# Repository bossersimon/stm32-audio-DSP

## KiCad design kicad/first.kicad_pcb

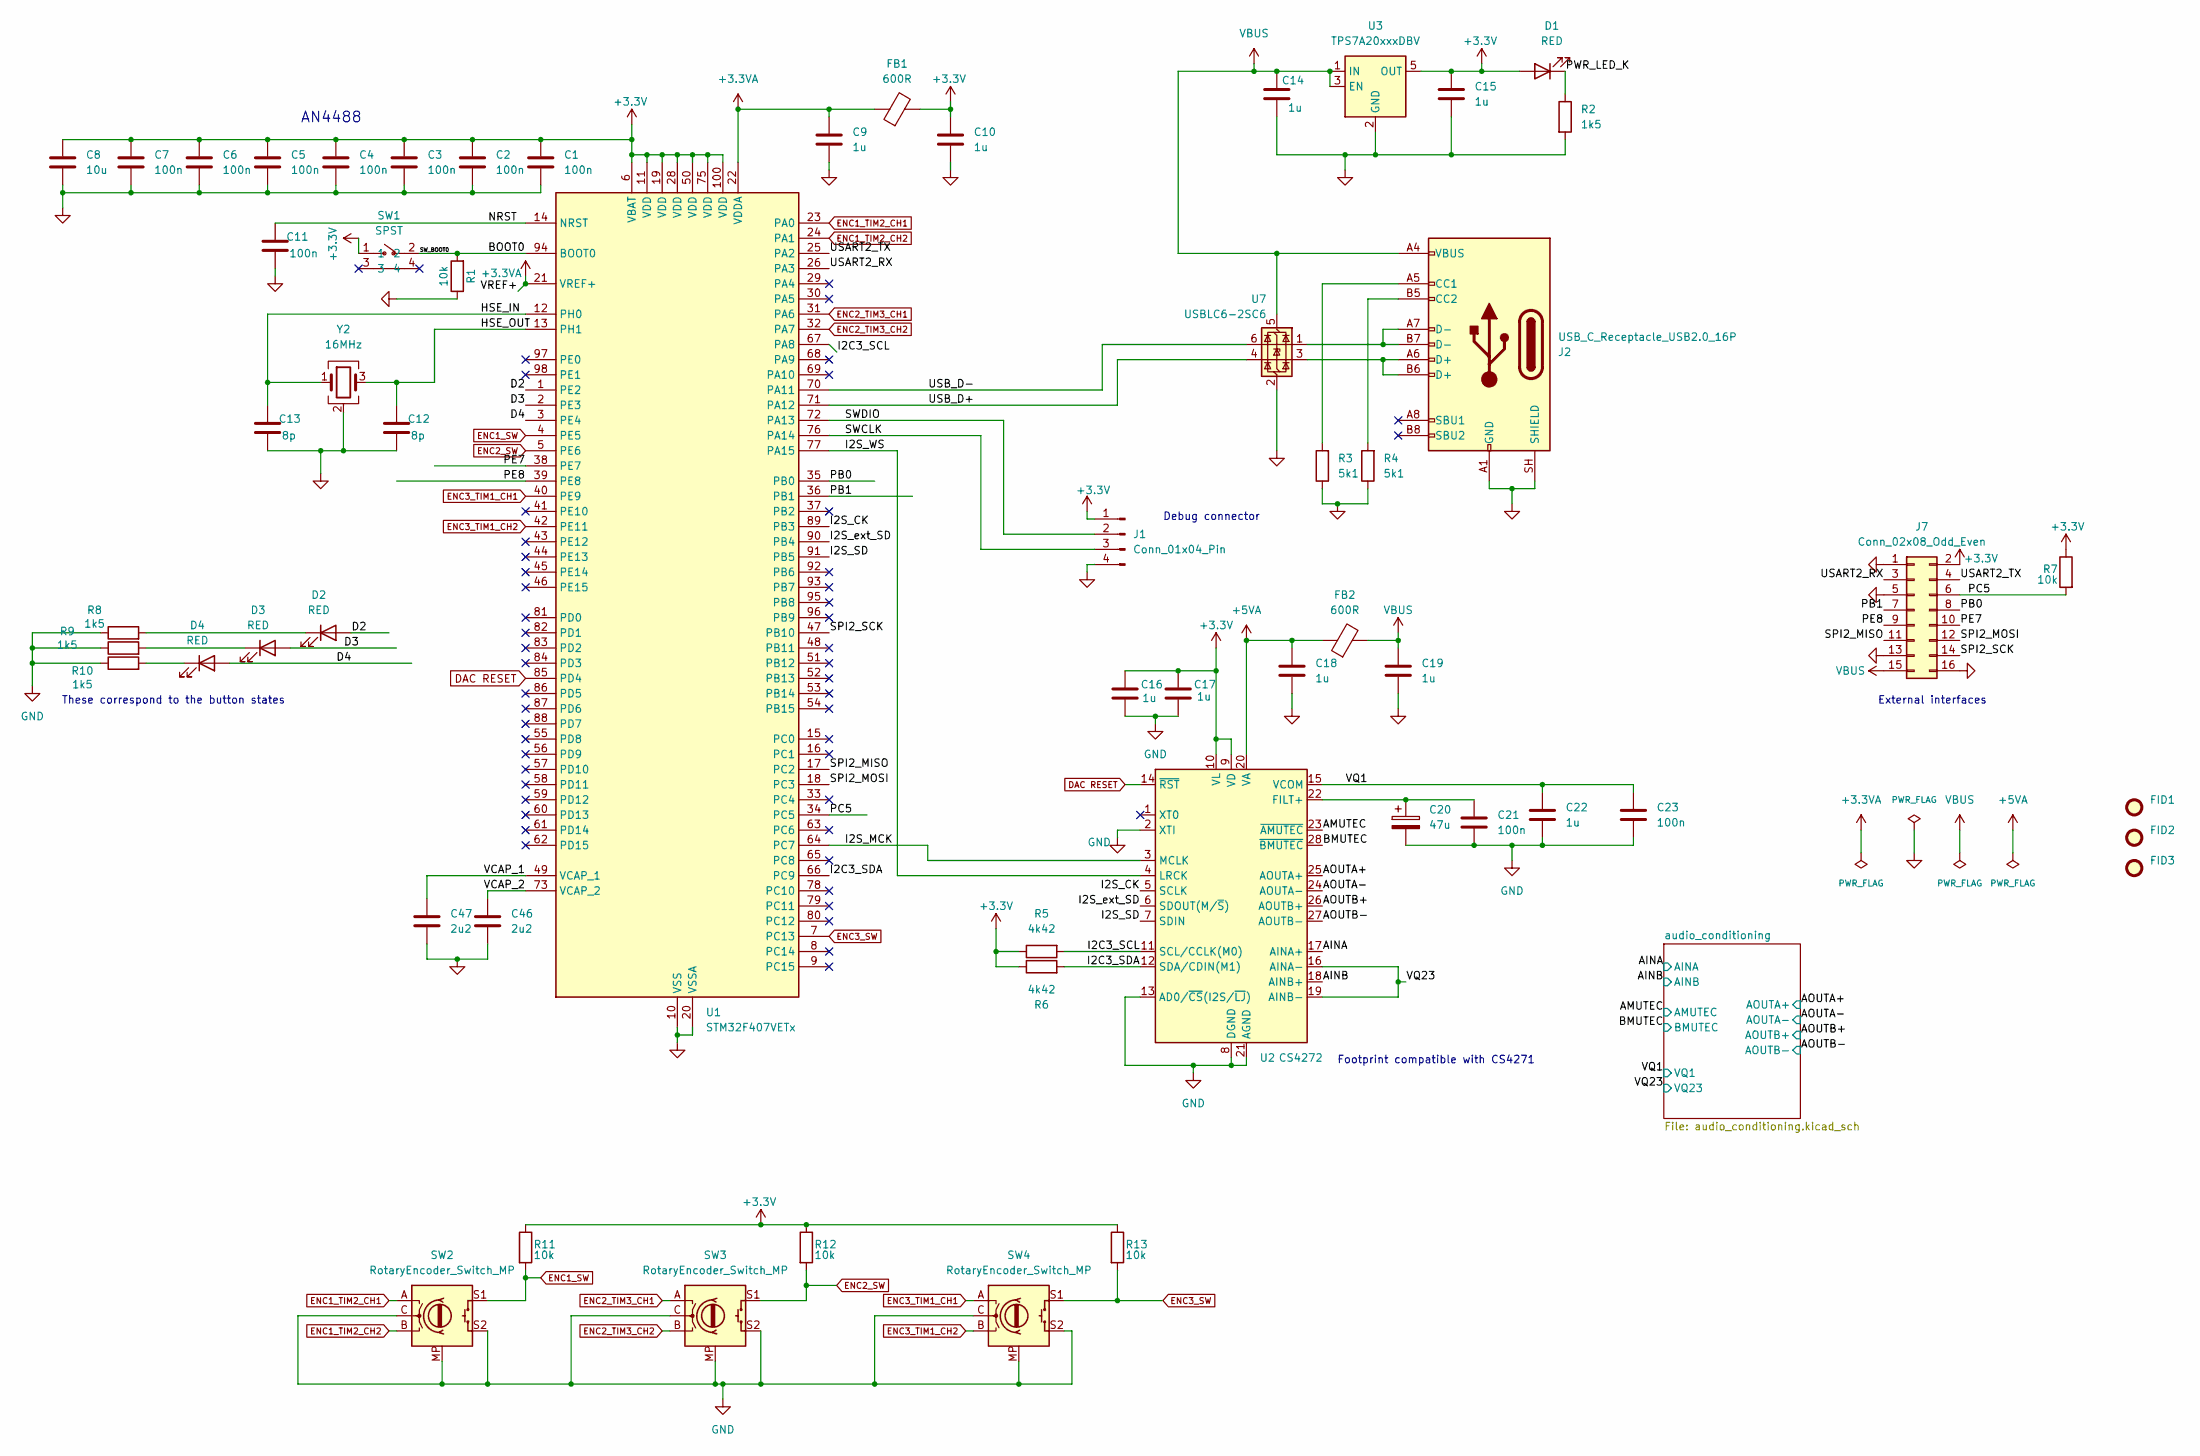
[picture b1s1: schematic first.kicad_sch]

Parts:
C1, C2, C3, C4, C5, C6, C7, C11, C21, C23: 100n; C_0402_1005Metric
C8: 10u; C_0603_1608Metric
C9, C10, C14, C15, C16, C17, C18, C19, C22: 1u; C_0402_1005Metric
C12, C13: 8p; C_0402_1005Metric
C20: 47u; CP_Elec_4x5.4
C46, C47: 2u2; C_0402_1005Metric
D1, D2, D3, D4: RED; LED_0603_1608Metric
FB1, FB2: 600R; L_0603_1608Metric
FID1, FID2, FID3: Fiducial; Fiducial_1mm_Mask3mm
J1: Conn_01x04_Pin; PinHeader_1x04_P2.54mm_Vertical
J2: USB_C_Receptacle_USB2.0_16P; USB_C_Receptacle_G-Switch_GT-USB-7010ASV
J7: Conn_02x08_Odd_Even; PinHeader_2x08_P2.54mm_Vertical
R1, R7, R11, R12, R13: 10k; R_0402_1005Metric
R2, R8, R9, R10: 1k5; R_0402_1005Metric
R3, R4: 5k1; R_0402_1005Metric
R5, R6: 4k42; R_0402_1005Metric
SW1: SPST; SW-SMD_TC-S3601-3.5-260G-F0.6; MPN TC-S3601-3.5-260G-F0.6; LCSC Part C49101620
SW2, SW3, SW4: RotaryEncoder_Switch_MP; RotaryEncoder_Alps_EC11E-Switch_Vertical_H20mm
U1: STM32F407VETx; LQFP-100_14x14mm_P0.5mm
U2: CS4272; TSSOP-28_4.4x9.7mm_P0.65mm
U3: TPS7A20xxxDBV; SOT-23-5
U7: USBLC6-2SC6; SOT-23-6
Y2: 16MHz; Crystal_SMD_3225-4Pin_3.2x2.5mm

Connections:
+3.3V: C1.1, C2.1, C3.1, C4.1, C5.1, C6.1, C7.1, C8.1, C10.1, C15.1, C16.1, C17.1, D1.2 (A), FB1.2, J1.1, J7.2, R5.1, R6.1, R7.1, R11.1, R12.1, R13.1, SW1.1, U1.6 (VBAT), U1.11 (VDD), U1.19 (VDD), U1.28 (VDD), U1.50 (VDD), U1.75 (VDD), U1.100 (VDD), U2.9 (VD), U2.10 (VL), U3.5 (OUT)
+3.3VA: C9.1, FB1.1, U1.21 (VREF+), U1.22 (VDDA)
+5VA: C18.1, FB2.1, U2.20 (VA); also elsewhere on the board
/AINA: U2.17 (AINA+); also elsewhere on the board
/AINB: U2.18 (AINB+); also elsewhere on the board
/AMUTEC: U2.23 (~AMUTEC); also elsewhere on the board
/AOUTA+: U2.25 (AOUTA+); also elsewhere on the board
/AOUTA-: U2.24 (AOUTA-); also elsewhere on the board
/AOUTB+: U2.26 (AOUTB+); also elsewhere on the board
/AOUTB-: U2.27 (AOUTB-); also elsewhere on the board
/BMUTEC: U2.28 (~BMUTEC); also elsewhere on the board
/BOOT0: R1.2, SW1.2, U1.94 (BOOT0)
/D2: D2.2 (A), U1.1 (PE2)
/D3: D3.2 (A), U1.2 (PE3)
/D4: D4.2 (A), U1.3 (PE4)
/HSE_IN: C13.1, U1.12 (PH0), Y2.1
/HSE_OUT: C12.1, U1.13 (PH1), Y2.3
/I2C3_SCL: R5.2, U1.67 (PA8), U2.11 (SCL/CCLK(M0))
/I2C3_SDA: R6.2, U1.66 (PC9), U2.12 (SDA/CDIN(M1))
/I2S_CK: U1.89 (PB3), U2.5 (SCLK)
/I2S_MCK: U1.64 (PC7), U2.3 (MCLK)
/I2S_SD: U1.91 (PB5), U2.7 (SDIN)
/I2S_WS: U1.77 (PA15), U2.4 (LRCK)
/I2S_ext_SD: U1.90 (PB4), U2.6 (SDOUT(M/~S))
/NRST: C11.1, U1.14 (NRST)
/PB0: J7.8, U1.35 (PB0)
/PB1: J7.7, U1.36 (PB1)
/PC5: J7.6, R7.2, U1.34 (PC5)
/PE7: J7.10, U1.38 (PE7)
/PE8: J7.9, U1.39 (PE8)
/PWR_LED_K: D1.1 (K), R2.1
/SPI2_MISO: J7.11, U1.17 (PC2)
/SPI2_MOSI: J7.12, U1.18 (PC3)
/SPI2_SCK: J7.14, U1.47 (PB10)
/SWCLK: J1.3, U1.76 (PA14)
/SWDIO: J1.2, U1.72 (PA13)
/USART2_RX: J7.3, U1.26 (PA3)
/USART2_TX: J7.4, U1.25 (PA2)
/USB_D+: U1.71 (PA12), U7.4 (I/O2)
/USB_D-: U1.70 (PA11), U7.6 (I/O1)
/VCAP_1: C47.2, U1.49 (VCAP_1)
/VCAP_2: C46.2, U1.73 (VCAP_2)
/VQ1: C22.1, C23.1, U2.15 (VCOM); also elsewhere on the board
/VQ23: U2.16 (AINA-), U2.19 (AINB-); also elsewhere on the board
DAC RESET: U1.85 (PD4), U2.14 (~RST)
ENC1_SW: R11.2, SW2.S1, U1.4 (PE5)
ENC1_TIM2_CH1: SW2.A, U1.23 (PA0)
ENC1_TIM2_CH2: SW2.B, U1.24 (PA1)
ENC2_SW: R12.2, SW3.S1, U1.5 (PE6)
ENC2_TIM3_CH1: SW3.A, U1.31 (PA6)
ENC2_TIM3_CH2: SW3.B, U1.32 (PA7)
ENC3_SW: R13.2, SW4.S1, U1.7 (PC13)
ENC3_TIM1_CH1: SW4.A, U1.40 (PE9)
ENC3_TIM1_CH2: SW4.B, U1.42 (PE11)
GND: C1.2, C2.2, C3.2, C4.2, C5.2, C6.2, C7.2, C8.2, C9.2, C10.2, C11.2, C12.2, C13.2, C14.2, C15.2, C16.2, C17.2, C18.2, C19.2, C20.2, C21.2, C22.2, C23.2, C46.1, C47.1, J1.4, J2.A1 (GND), J2.A12 (GND), J2.B1 (GND), J2.B12 (GND), J2.SH (SHIELD), J7.1, J7.5, J7.13, J7.16, R1.1, R2.2, R3.1, R4.1, R8.1, R9.1, R10.1, SW2.C, SW2.MP, SW2.S2, SW3.C, SW3.MP, SW3.S2, SW4.C, SW4.MP, SW4.S2, U1.10 (VSS), U1.20 (VSSA), U1.27 (VSS), U1.74 (VSS), U1.99 (VSS), U2.2 (XTI), U2.8 (DGND), U2.13 (AD0/~CS(I2S/~LJ)), U2.21 (AGND), U3.2 (GND), U7.2 (GND), Y2.2 (G), Y2.4 (G); also elsewhere on the board
unnamed: D2.1 (K), R8.2
unnamed: D3.1 (K), R9.2
unnamed: D4.1 (K), R10.2
unnamed: J2.A5 (CC1), R3.2
unnamed: J2.B5 (CC2), R4.2
unnamed: J2.A6 (D+), J2.B6 (D+), U7.3 (I/O2)
unnamed: J2.A7 (D-), J2.B7 (D-), U7.1 (I/O1)
unnamed: C20.1, C21.1, U2.22 (FILT+)
VBUS: C14.1, C19.1, FB2.2, J2.A4 (VBUS), J2.A9 (VBUS), J2.B4 (VBUS), J2.B9 (VBUS), J7.15, U3.1 (IN), U3.3 (EN), U7.5 (VBUS)

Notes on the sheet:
AN4488
These correspond to the button states
Footprint compatible with CS4271
Debug connector
External interfaces

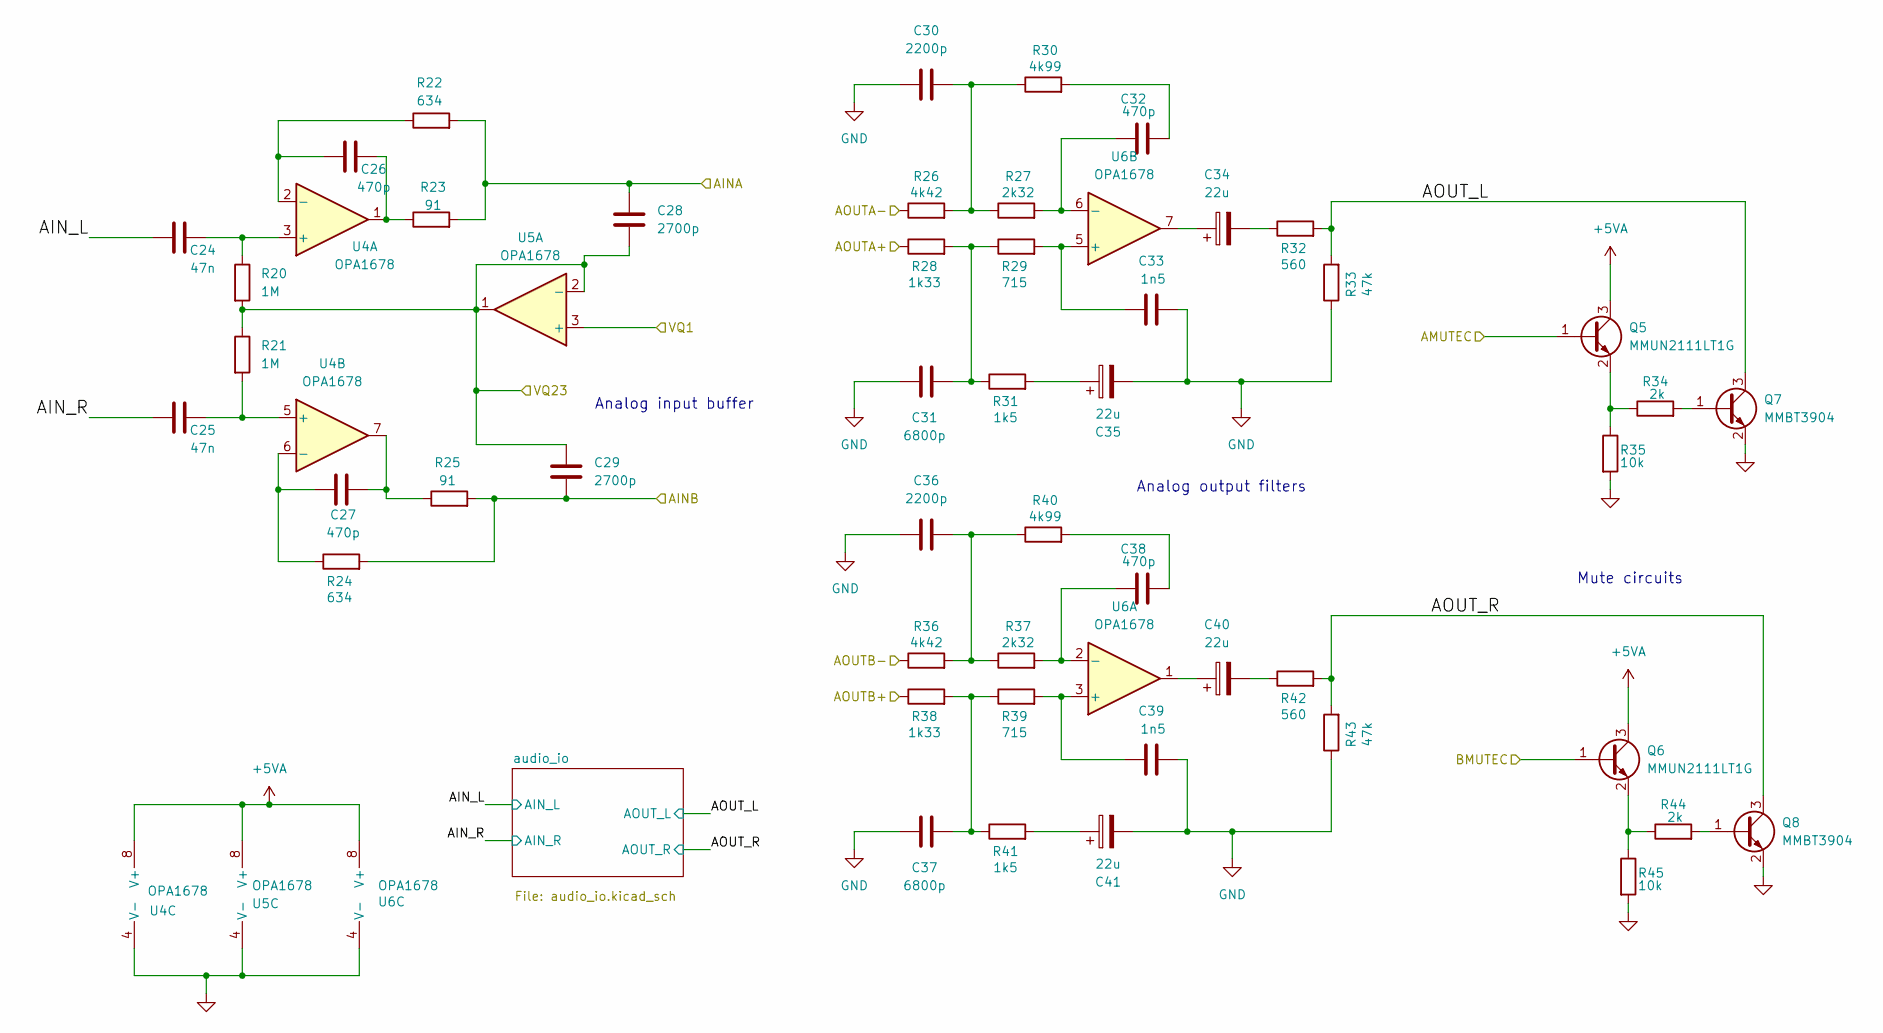
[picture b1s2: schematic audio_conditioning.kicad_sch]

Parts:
C24, C25: 47n; C_0805_2012Metric
C26, C27, C32, C38: 470p; C_0402_1005Metric
C28, C29: 2700p; C_0603_1608Metric
C30, C36: 2200p; C_0603_1608Metric
C31, C37: 6800p; C_0603_1608Metric
C33, C39: 1n5; C_0603_1608Metric
C34, C35, C40, C41: 22u; CP_Elec_4x5.4
Q5, Q6: MMUN2111LT1G; SOT-23
Q7, Q8: MMBT3904; SOT-23
R20, R21: 1M; R_0402_1005Metric
R22, R24: 634; R_0402_1005Metric
R23, R25: 91; R_0402_1005Metric
R26, R36: 4k42; R_0402_1005Metric
R27, R37: 2k32; R_0402_1005Metric
R28, R38: 1k33; R_0402_1005Metric
R29, R39: 715; R_0402_1005Metric
R30, R40: 4k99; R_0402_1005Metric
R31, R41: 1k5; R_0402_1005Metric
R32, R42: 560; R_0402_1005Metric
R33, R43: 47k; R_0402_1005Metric
R34, R44: 2k; R_0402_1005Metric
R35, R45: 10k; R_0402_1005Metric
U4, U5, U6: OPA1678; SOIC-8_3.9x4.9mm_P1.27mm

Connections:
+5VA: Q5.3 (C), Q6.3 (C), U4.8 (V+), U5.8 (V+), U6.8 (V+); also elsewhere on the board
/AINA: C28.1, R22.2, R23.2; also elsewhere on the board
/AINB: C29.2, R24.2, R25.2; also elsewhere on the board
/AMUTEC: Q5.1 (B); also elsewhere on the board
/AOUTA+: R28.1; also elsewhere on the board
/AOUTA-: R26.1; also elsewhere on the board
/AOUTB+: R38.1; also elsewhere on the board
/AOUTB-: R36.1; also elsewhere on the board
/BMUTEC: Q6.1 (B); also elsewhere on the board
/VQ1: U5.3 (+); also elsewhere on the board
/VQ23: C28.2, C29.1, R20.2, R21.1, U5.1, U5.2 (-); also elsewhere on the board
/audio_conditioning/AIN_L: C24.2; also elsewhere on the board
/audio_conditioning/AIN_R: C25.2; also elsewhere on the board
/audio_conditioning/AOUT_L: Q7.3 (C), R32.2, R33.2; also elsewhere on the board
/audio_conditioning/AOUT_R: Q8.3 (C), R42.2, R43.2; also elsewhere on the board
GND: C30.2, C31.2, C33.1, C35.2, C36.2, C37.2, C39.1, C41.2, Q7.2 (E), Q8.2 (E), R33.1, R35.2, R43.1, R45.2, U4.4 (V-), U5.4 (V-), U6.4 (V-); also elsewhere on the board
unnamed: C26.1, R23.1, U4.1
unnamed: C27.1, R25.1, U4.7
unnamed: C30.1, R26.2, R27.1, R30.1
unnamed: C31.1, R28.2, R29.1, R31.1
unnamed: C32.1, R30.2
unnamed: C34.1, U6.7
unnamed: C34.2, R32.1
unnamed: C35.1, R31.2
unnamed: C36.1, R36.2, R37.1, R40.1
unnamed: C37.1, R38.2, R39.1, R41.1
unnamed: C38.1, R40.2
unnamed: C40.1, U6.1
unnamed: C40.2, R42.1
unnamed: C41.1, R41.2
unnamed: Q5.2 (E), R34.1, R35.1
unnamed: Q6.2 (E), R44.1, R45.1
unnamed: Q7.1 (B), R34.2
unnamed: Q8.1 (B), R44.2
unnamed: C24.1, R20.1, U4.3 (+)
unnamed: C26.2, R22.1, U4.2 (-)
unnamed: C25.1, R21.2, U4.5 (+)
unnamed: C27.2, R24.1, U4.6 (-)
unnamed: C39.2, R39.2, U6.3 (+)
unnamed: C38.2, R37.2, U6.2 (-)
unnamed: C33.2, R29.2, U6.5 (+)
unnamed: C32.2, R27.2, U6.6 (-)

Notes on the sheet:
Analog output filters
Analog input buffer
Mute circuits

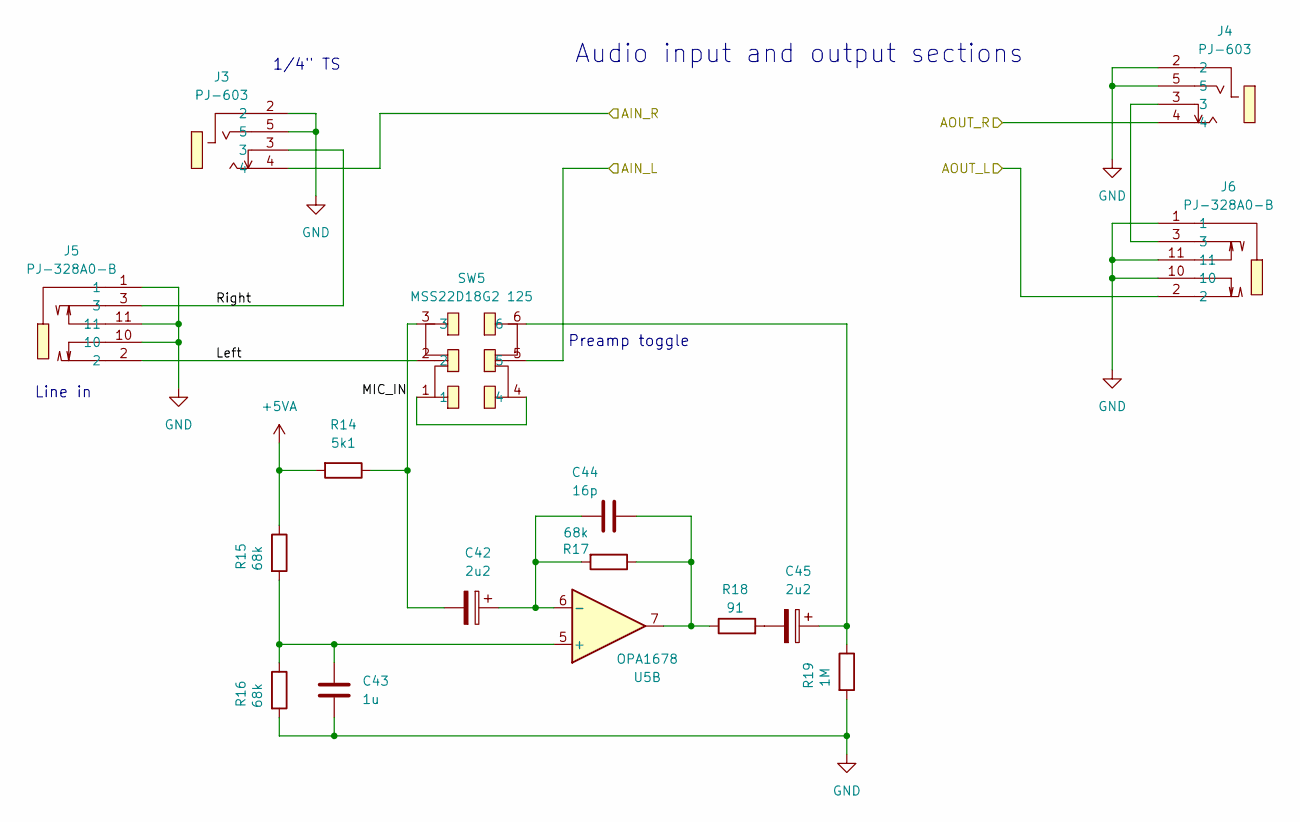
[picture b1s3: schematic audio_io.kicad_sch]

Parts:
C42, C45: 2u2; CP_Elec_4x5.4
C43: 1u; C_0402_1005Metric
C44: 16p; C_0402_1005Metric
J3, J4: PJ-603; AUDIO-TH_PJ-603; MPN PJ-603环保; LCSC Part C309272
J5, J6: PJ-328A0-B; AUDIO-TH_PJ-328A0-B; MPN PJ-328A0-B; LCSC Part C381129
R14: 5k1; R_0402_1005Metric
R15, R16, R17: 68k; R_0402_1005Metric
R18: 91; R_0402_1005Metric
R19: 1M; R_0402_1005Metric
SW5: MSS22D18G2 125; SW-TH_SHOU_MSS22D18G2; MPN MSS22D18G2 125; LCSC Part C2906278
U5: OPA1678; SOIC-8_3.9x4.9mm_P1.27mm

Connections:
+5VA: R14.2, R15.1; also elsewhere on the board
/audio_conditioning/AIN_L: SW5.5; also elsewhere on the board
/audio_conditioning/AIN_R: J3.4; also elsewhere on the board
/audio_conditioning/AOUT_L: J6.2; also elsewhere on the board
/audio_conditioning/AOUT_R: J4.4; also elsewhere on the board
/audio_conditioning/audio_io/Left: J5.2, SW5.2
/audio_conditioning/audio_io/MIC_IN: C42.2, R14.1, SW5.3
/audio_conditioning/audio_io/Right: J3.3, J5.3
GND: C43.2, J3.2, J3.5, J4.2, J4.5, J5.1, J5.10, J5.11, J6.1, J6.10, J6.11, R16.2, R19.2; also elsewhere on the board
unnamed: C44.2, R17.1, R18.1, U5.7
unnamed: C45.1, R19.1, SW5.6
unnamed: C45.2, R18.2
unnamed: J4.3, J6.3
unnamed: SW5.1, SW5.4
unnamed: C43.1, R15.2, R16.1, U5.5 (+)
unnamed: C42.1, C44.1, R17.2, U5.6 (-)

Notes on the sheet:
Preamp toggle
Audio input and output sections
1/4" TS
Line in

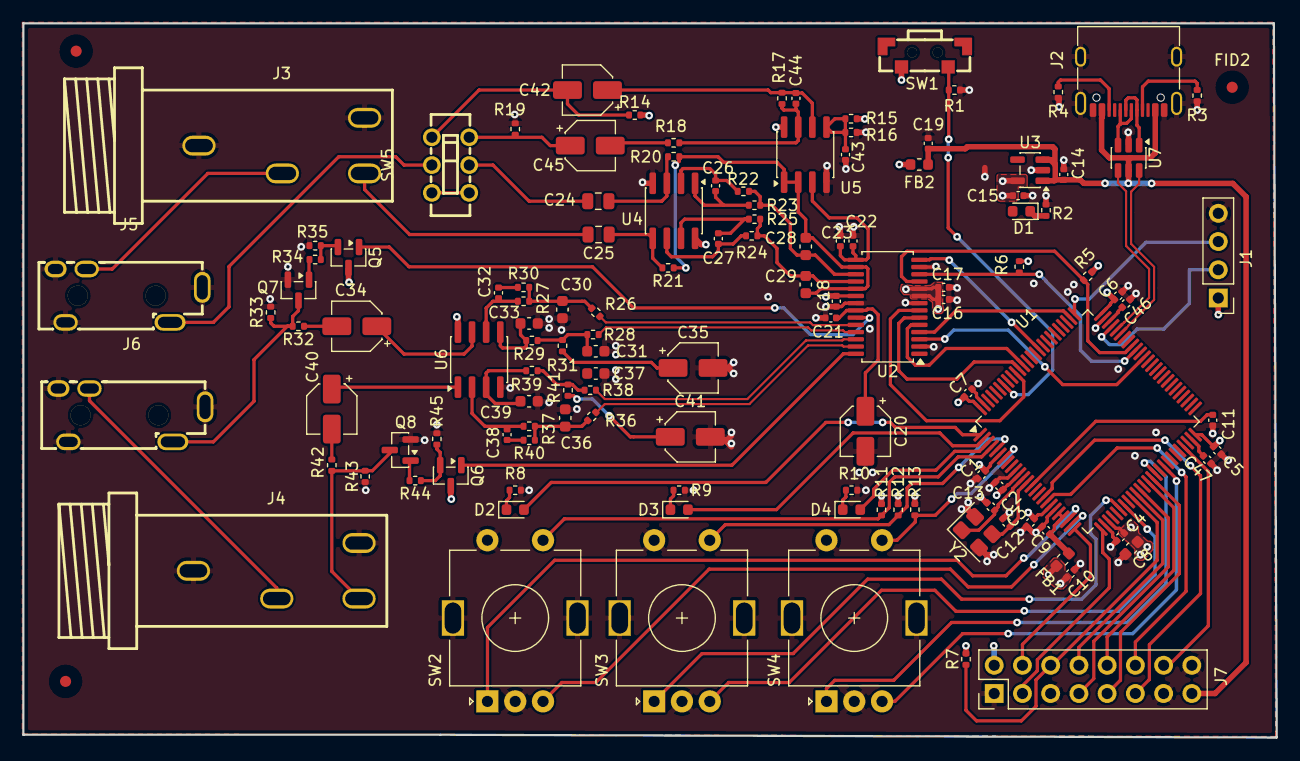
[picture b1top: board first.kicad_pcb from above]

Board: 4 copper layers, 112.8 x 64.2 mm, 125 parts (0 on the bottom side), 104 nets.

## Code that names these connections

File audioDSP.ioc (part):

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Mcu.Name=STM32F407V(E-G)Tx
Mcu.Package=LQFP100
Mcu.UserName=STM32F407VGTx
PA0-WKUP.Signal=S_TIM2_CH1_ETR
PA1.Signal=S_TIM2_CH2
PA11.Mode=Device_Only
PA11.Signal=USB_OTG_FS_DM
PA12.Mode=Device_Only
PA12.Signal=USB_OTG_FS_DP
PA13.Mode=Serial_Wire
PA13.Signal=SYS_JTMS-SWDIO
PA14.Mode=Serial_Wire
PA14.Signal=SYS_JTCK-SWCLK
PA15.Mode=Full_Duplex_Master
PA15.Signal=I2S3_WS
PA2.GPIOParameters=GPIO_Label
PA2.GPIO_Label=ENC1_SW
PA2.Signal=GPIO_Input
PA5.GPIOParameters=GPIO_Label
PA5.GPIO_Label=ENC2_SW
PA5.Signal=GPIO_Input
PA6.Signal=S_TIM3_CH1
PA7.Signal=S_TIM3_CH2
PA9.Mode=Activate_VBUS
PA9.Signal=USB_OTG_FS_VBUS
PB0.Signal=ADCx_IN8
PB1.Signal=ADCx_IN9
PB10.Mode=I2C
PB10.Signal=I2C2_SCL
PB11.Mode=I2C
PB11.Signal=I2C2_SDA
PB13.Mode=Full_Duplex_Master
PB13.Signal=SPI2_SCK
PB3.Mode=Full_Duplex_Master
PB3.Signal=I2S3_CK
PB4.Mode=Full_Duplex_Master
PB4.Signal=I2S3_ext_SD
PB5.Mode=Full_Duplex_Master
PB5.Signal=I2S3_SD
PB8.Mode=I2C
PB8.Signal=I2C1_SCL
PB9.Mode=I2C
PB9.Signal=I2C1_SDA
PC2.Mode=Full_Duplex_Master
PC2.Signal=SPI2_MISO
PC3.Mode=Full_Duplex_Master
PC3.Signal=SPI2_MOSI
PC5.Signal=ADCx_IN15
PC7.Mode=Master_Clock_Activated
PC7.Signal=I2S3_MCK
PD12.Signal=GPIO_Output
PD13.Signal=GPIO_Output
PD14.Signal=GPIO_Output
PD15.Signal=GPIO_Output
PD4.GPIOParameters=GPIO_Label
PD4.GPIO_Label=DAC RESET
PD4.Signal=GPIO_Output
PD8.Mode=Asynchronous
PD8.Signal=USART3_TX
PD9.Mode=Asynchronous
PD9.Signal=USART3_RX
PE10.GPIOParameters=GPIO_Label
PE10.GPIO_Label=ENC3_SW
PE10.Signal=GPIO_Input
PE11.Signal=S_TIM1_CH2
PE7.Signal=GPIO_Input
PE9.Signal=S_TIM1_CH1
PH0-OSC_IN.Mode=HSE-External-Oscillator
PH0-OSC_IN.Signal=RCC_OSC_IN
PH1-OSC_OUT.Mode=HSE-External-Oscillator
PH1-OSC_OUT.Signal=RCC_OSC_OUT
RCC.HSE_VALUE=16000000
RCC.SYSCLKFreq_VALUE=168000000
RCC.SYSCLKSource=RCC_SYSCLKSOURCE_PLLCLK
board=custom

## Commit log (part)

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2026-04-07 USER PV for in/out buffers
2026-04-07 configured output DMA for I2S
2026-04-07 DMA buffers + pointers
2026-04-07 added DMA callbacks (empty) and started DMA stream in main
2026-04-07 function placeholders
2026-04-08 edited callbacks + time and sample rate variables
2026-04-08 regenerated MX code, mainly clock and DMA I2S config
2026-04-08 generate_DMA function, replaced t with phase (not tested)
2026-04-14 removed ADC for now, configured I2S TX only, moved sine generation into main
2026-04-20 DAC codec + Audio IO definitions
2026-04-20 include codec in Cmake
2026-04-20 disabled full duplex mode for now, added codec inits, phase variables changed to float, defined DAC I2C address
2026-04-20 now plays some nice music
2026-04-20 works will full duplex enabled
2026-04-20 changed usb device class to audio
2026-05-04 Start of first schematic
2026-05-05 something
2026-05-05 kicad folder
2026-05-06 added LDO
2026-05-06 component notes
2026-05-06 easyeda2kicad script
2026-05-25 audio codec + input audio buffers
2026-05-26 analog output filters
2026-05-28 working on codec supplies
2026-06-21 parts for mute control circuit, need to rethink analog power input
